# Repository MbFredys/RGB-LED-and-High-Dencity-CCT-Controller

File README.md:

# RGB + CCT LED Controller

Five-channel RGB and tunable-white LED-controller PCB based on the ESP32-C3.

> **Project status:** Design and manufacturing documentation completed. The PCB has not been fabricated, thermally characterized, or electrically validated under load.

## Project objective

The project explores a compact controller capable of driving RGB, warm-white, and cool-white LED channels while integrating wireless control, local power conversion, and USB-C programming.

## Hardware architecture

- **Controller:** ESP32-C3-WROOM-02
- **Outputs:** Five low-side PWM channels: R, G, B, warm white, and cool white
- **Switching devices:** IRLZ44N MOSFETs
- **Power input:** 12 V nominal
- **Conversion:** LM2678T-ADJ buck stage and TPS7A20 3.3 V regulation
- **Programming:** USB-C interface
- **Protection:** Input fuse and transient-protection components
- **Connections:** Dedicated RGB and CCT output connectors

## Engineering work

- Defined the functional and power architecture
- Selected the controller, switching devices, regulators, and protection components
- Developed the schematic and PCB layout in KiCad
- Separated high-current and logic routing
- Prepared the BOM and manufacturing documentation

## Key design considerations

- MOSFET conduction losses and gate drive at 3.3 V
- Copper width, connector rating, and total current distribution
- Regulator thermal performance
- PWM return-current paths
- Bulk capacitance near LED outputs
- ESP32 antenna clearance and noise coupling

## Validation still required

Physical testing is required to establish:

- Safe continuous current per channel
- MOSFET and regulator temperatures
- Voltage-drop and connector performance
- PWM behavior with representative LED strips
- Wireless performance during switching
- Protection response and EMC/EMI behavior

The intended current ratings are design targets and must not be treated as validated operating limits.

## License

Licensed under CERN-OHL-W-2.0.

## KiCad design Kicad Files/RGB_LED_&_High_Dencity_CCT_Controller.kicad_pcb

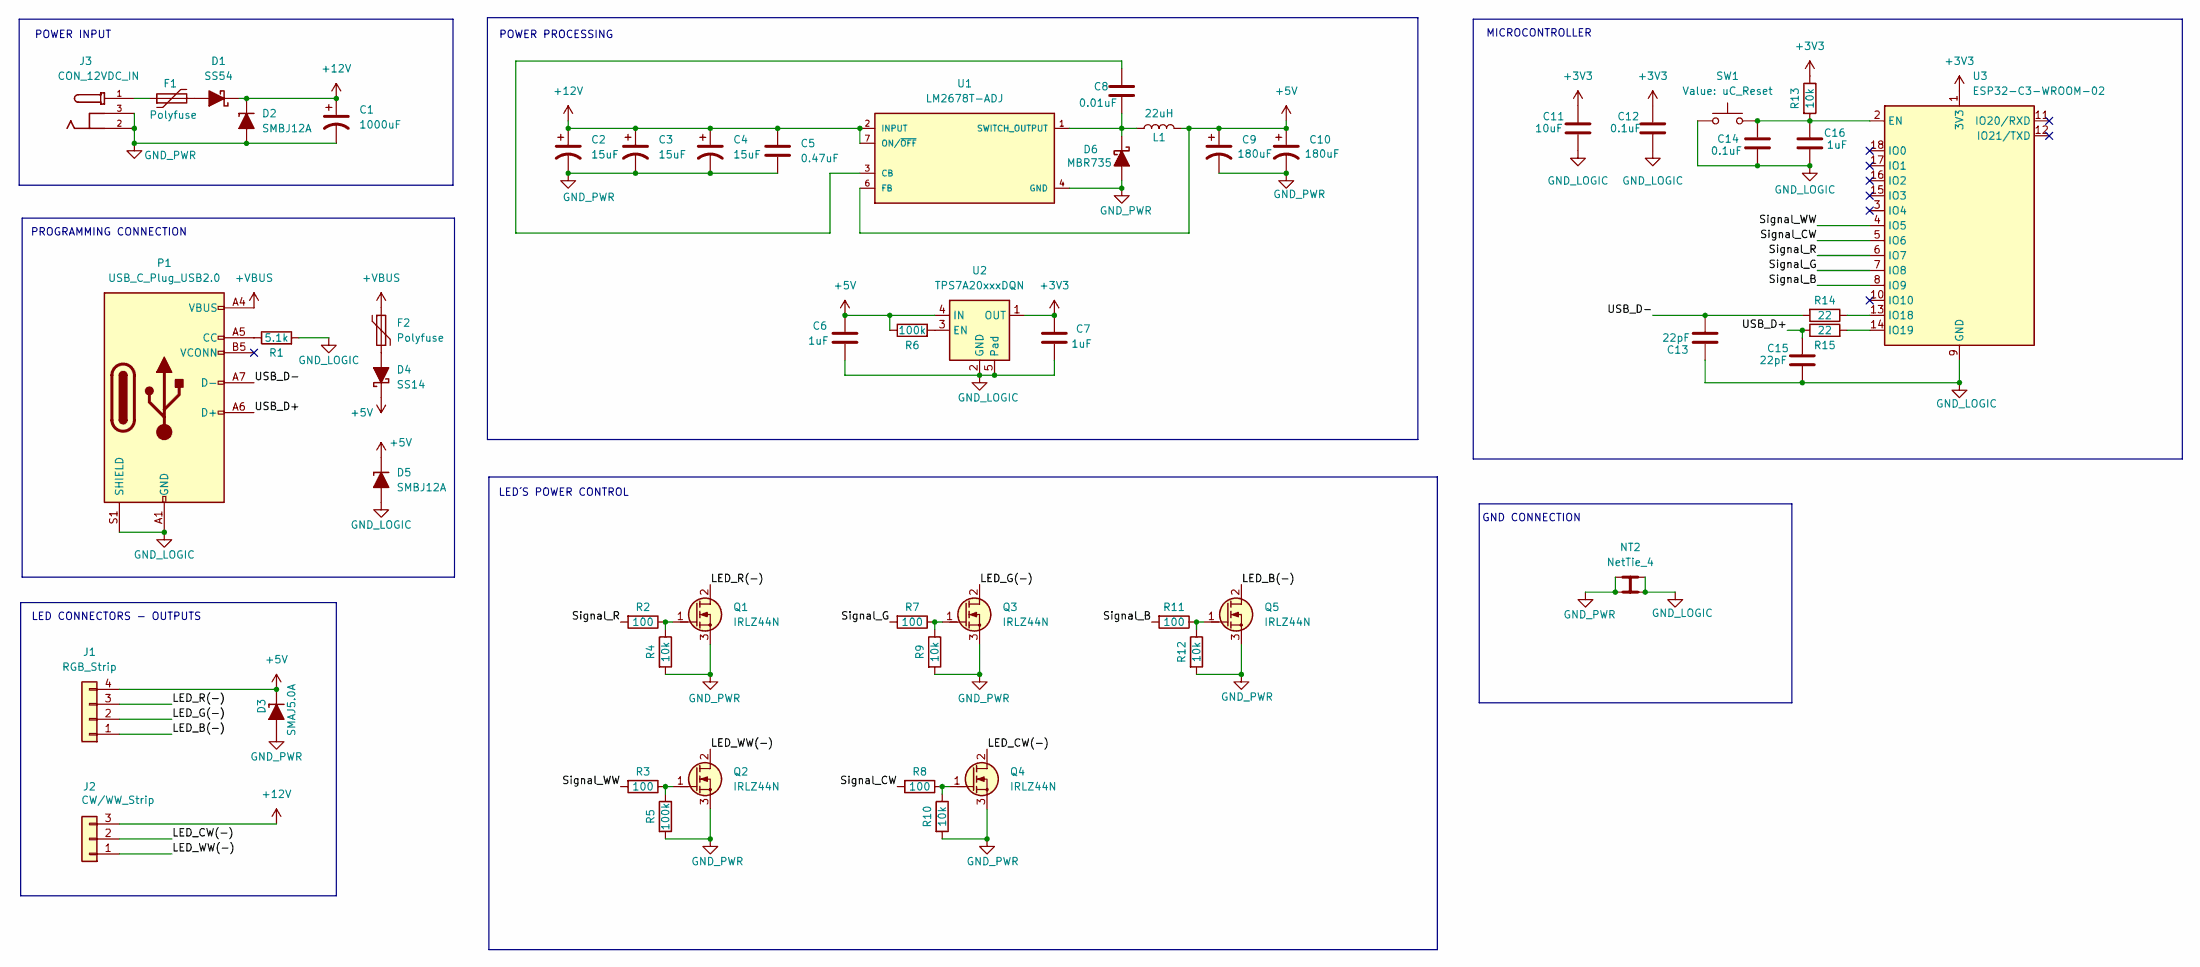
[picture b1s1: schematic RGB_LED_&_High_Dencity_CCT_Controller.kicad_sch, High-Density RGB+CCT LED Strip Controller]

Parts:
C1: 1000uF; CAPPRD500W60D1000H1300; MPN 16SEPF1000M; LCSC PN C128486
C2, C3, C4: 15uF; CAPPRD200W45D500H700; MPN EEA-GA1E150; LCSC PN C1580740
C5: 0.47uF; C_0805_2012Metric; MPN GRM155R71C474KE01D; LCSC PN C471404
C6, C7: 1uF; C_0603_1608Metric; MPN CL10A105KB8NNNC; LCSC PN C15849
C8: 0.01uF; CAPRR750W60L1030T440H750; MPN ECQE4123JF; LCSC PN C48579278
C9, C10: 180uF; CAP_EEEFNE181XUV; MPN EEEFNE181XUV; LCSC PN C540948
C11: 10uF; C_0603_1608Metric; MPN GRM155R71C474KE01D; LCSC PN 0402
C12, C14: 0.1uF; C_0603_1608Metric; MPN GRM155R71C474KE01D; LCSC PN 0402
C13, C15: 22pF; C_0603_1608Metric; MPN GRM155R71C474KE01D; LCSC PN 0402
C16: 1uF; C_0603_1608Metric; MPN GRM155R71C474KE01D; LCSC PN 0402
D1: SS54; D_SMC; MPN SS54; LCSC PN C22452
D2: SMBJ12A; D_SMB; MPN SMBJ12A; LCSC PN C151251
D3: SMAJ5.0A; D_SMA; MPN SMAJ5.0A; LCSC PN C83329
D4: SS14; D_SMA
D5: SMBJ12A; D_SMB
D6: MBR735; TO-220-2_Vertical_KA; MPN MBR735; LCSC PN C3759044
F1: Polyfuse; FUSC7351X170N; MPN 0ZCF0600FF2C; LCSC PN C20040854
F2: Polyfuse; FUSC1608X100N
J1: RGB_Strip; PhoenixContact_MCV_1,5_4-G-5.08_1x04_P5.08mm_Vertical
J2: CW/WW_Strip; PhoenixContact_MCV_1,5_3-G-5.08_1x03_P5.08mm_Vertical
J3: CON_12VDC_IN; MPD_EJ503A; MPN EJ503A; LCSC PN C3095117
L1: 22uH; IND_XAL6060-223MEB; MPN FXL1040-220-M; LCSC PN C475917
NT2: NetTie_4; NetTie-4_THT_Pad1.0mm
P1: USB_C_Plug_USB2.0; USB_C_Receptacle_GCT_USB4105-xx-A_16P_TopMnt_Horizontal
Q1, Q2, Q3, Q4, Q5: IRLZ44N; TO254P1524X483-4N; MPN IRLZ44NSPBF-VB; LCSC PN C19188232
R1: 5.1k; R_0603_1608Metric
R2, R3, R7, R8, R11: 100; R_0402_1005Metric
R4, R9, R10, R12, R13: 10k; R_0603_1608Metric
R5: 100k; R_0603_1608Metric
R6: 100k; R_0805_2012Metric; MPN RC0805FR-07100KL; LCSC PN C96346
R14, R15: 22; R_0402_1005Metric
SW1: uC_Reset; SW_Push_SPST_NO_Alps_SKRK
U1: LM2678T-ADJ; TO127P1041X469X2199-7N
U2: TPS7A20xxxDQN; Texas_X2SON-4_1x1mm_P0.65mm
U3: ESP32-C3-WROOM-02; MPN ESP32-C3-WROOM-02-N4; LCSC PN C2934560

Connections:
+3V3: C7.1, C11.1, C12.1, R13.1, U2.1 (OUT), U3.1 (3V3)
+5V: C6.1, C9.1, C10.1, D3.1 (K), D4.1 (K), D5.1 (K), J1.4, L1.2, R6.1, U1.6 (FB), U2.4 (IN)
+12V: C1.1, C2.1, C3.1, C4.1, C5.1, D1.1 (K), D2.1 (K), J2.3, U1.2 (INPUT), U1.7 (ON/~OFF)
+VBUS: F2.1, P1.A4 (VBUS), P1.A9 (VBUS), P1.B4 (VBUS), P1.B9 (VBUS)
/LED_B(-): J1.1, Q5.2 (D)
/LED_CW(-): J2.2, Q4.2 (D)
/LED_G(-): J1.2, Q3.2 (D)
/LED_R(-): J1.3, Q1.2 (D)
/LED_WW(-): J2.1, Q2.2 (D)
/Signal_B: R11.2, U3.8 (IO9)
/Signal_CW: R8.2, U3.5 (IO6)
/Signal_G: R7.2, U3.7 (IO8)
/Signal_R: R2.2, U3.6 (IO7)
/Signal_WW: R3.2, U3.4 (IO5)
/USB_D+: C15.1, P1.A6 (D+), R15.1
/USB_D-: C13.1, P1.A7 (D-), R14.2
GND_LOGIC: C6.2, C7.2, C11.2, C12.2, C13.2, C14.1, C15.2, C16.2, D5.2 (A), NT2.2, NT2.4, P1.A1 (GND), P1.A12 (GND), P1.B1 (GND), P1.B12 (GND), P1.S1 (SHIELD), R1.2, SW1.1, U2.2 (GND), U2.5 (Pad), U3.9 (GND), U3.19 (GND)
GND_PWR: C1.2, C2.2, C3.2, C4.2, C5.2, C9.2, C10.2, D2.2 (A), D3.2 (A), D6.2 (A), J3.2, J3.3, NT2.1, NT2.3, Q1.3 (S), Q2.3 (S), Q3.3 (S), Q4.3 (S), Q5.3 (S), R4.2, R5.2, R9.2, R10.2, R12.2, U1.4 (GND)
unnamed: D1.2 (A), F1.2
unnamed: D4.2 (A), F2.2
unnamed: C8.2, D6.1 (K), L1.1, U1.1 (SWITCH_OUTPUT)
unnamed: F1.1, J3.1
unnamed: P1.A5 (CC), R1.1
unnamed: Q1.1 (G), R2.1, R4.1
unnamed: Q2.1 (G), R3.1, R5.1
unnamed: Q3.1 (G), R7.1, R9.1
unnamed: Q4.1 (G), R8.1, R10.1
unnamed: Q5.1 (G), R11.1, R12.1
unnamed: C8.1, U1.3 (CB)
unnamed: R6.2, U2.3 (EN)
unnamed: C14.2, C16.1, R13.2, SW1.2, U3.2 (EN)
unnamed: R14.1, U3.13 (IO18)
unnamed: R15.2, U3.14 (IO19)

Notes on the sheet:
POWER PROCESSING
POWER INPUT
GND CONNECTION
LED CONNECTORS - OUTPUTS
LED´S POWER CONTROL
MICROCONTROLLER
PROGRAMMING CONNECTION

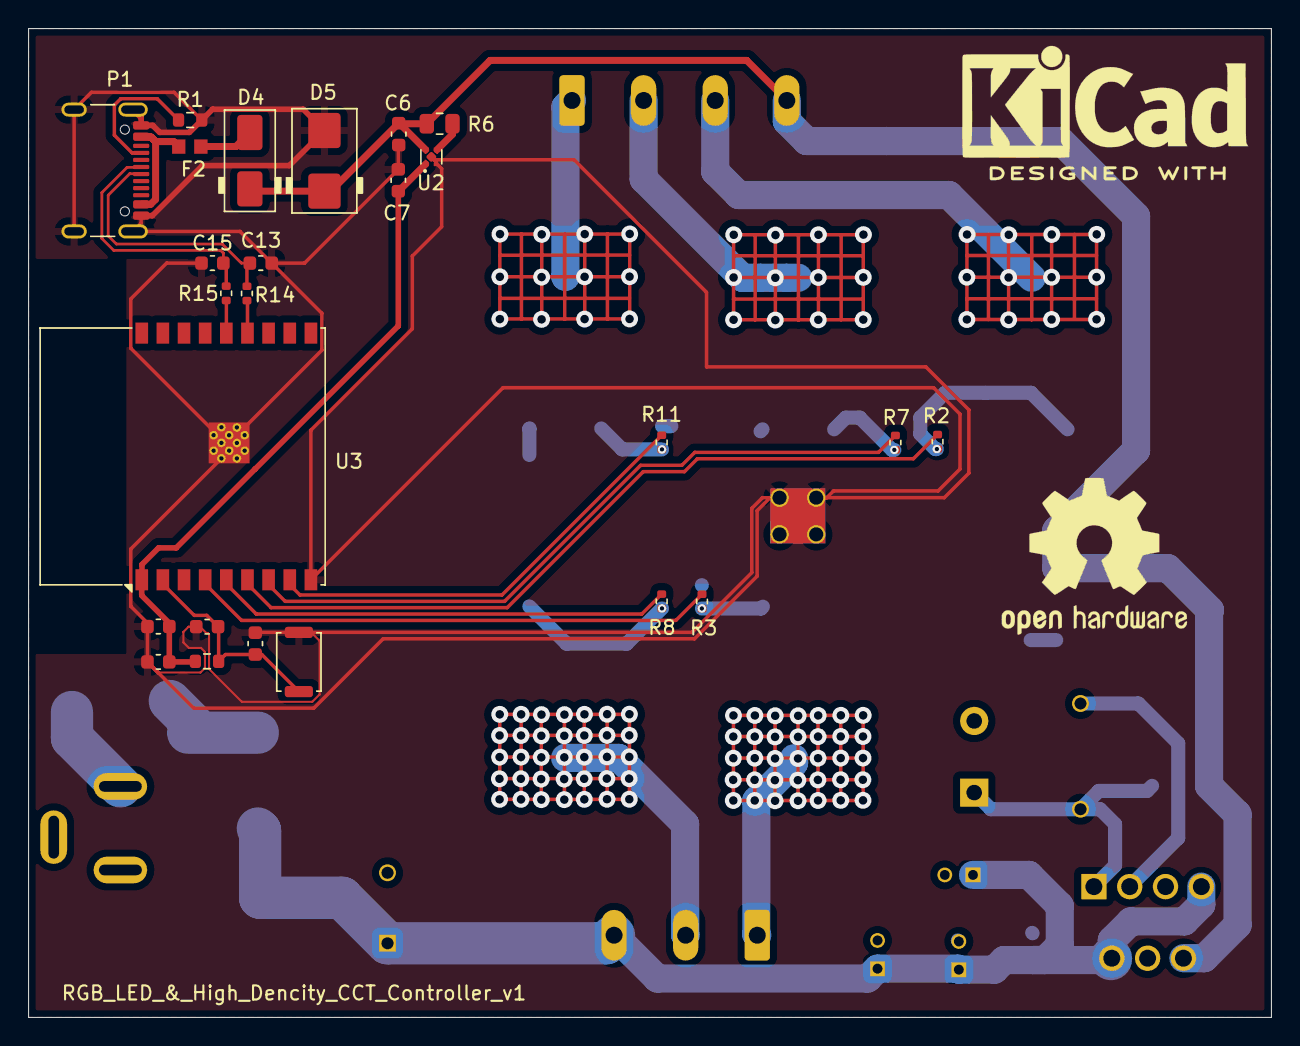
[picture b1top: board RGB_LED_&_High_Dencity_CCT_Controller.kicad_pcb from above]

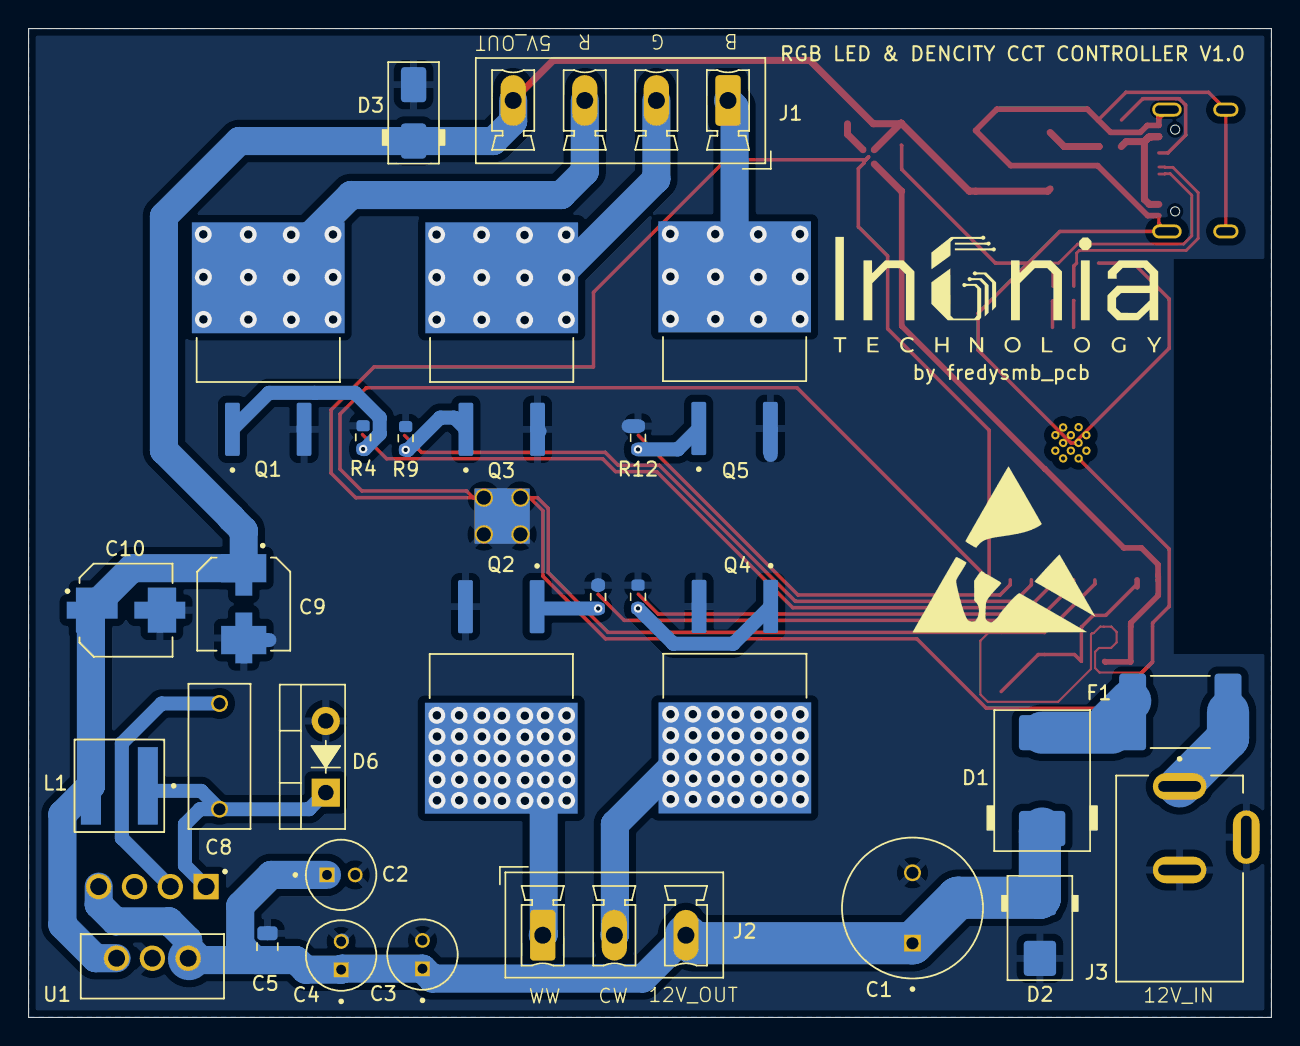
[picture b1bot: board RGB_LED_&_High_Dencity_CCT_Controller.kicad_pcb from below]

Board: 2 copper layers, 88.2 x 70.2 mm, 54 parts (28 on the bottom side), 33 nets.

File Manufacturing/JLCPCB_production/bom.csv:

Designator,Footprint,Quantity,Value,LCSC Part #
C1,CAPPRD500W60D1000H1300,1,1000uF,
"C10, C9",CAP_EEEFNE181XUV,2,180uF,
C11,0603,1,10uF,
"C12, C14",0603,2,0.1uF,
"C13, C15",0603,2,22pF,
"C16, C6, C7",0603,3,1uF,
"C2, C3, C4",CAPPRD200W45D500H700,3,15uF,
C5,0805,1,0.47uF,
C8,CAPRR750W60L1030T440H750,1,0.01uF,
D1,D_SMC,1,SS54,
"D2, D5",D_SMB,2,SMBJ12A,
D3,D_SMA,1,SMAJ5.0A,
D4,D_SMA,1,SS14,
D6,TO-220-2_Vertical_KA,1,MBR735,
F1,FUSC7351X170N,1,Polyfuse,
F2,FUSC1608X100N,1,Polyfuse,
J1,"PhoenixContact_MCV_1,5_4-G-5.08_1x04_P5.08mm_Vertical",1,RGB_Strip,
J2,"PhoenixContact_MCV_1,5_3-G-5.08_1x03_P5.08mm_Vertical",1,CW/WW_Strip,
J3,MPD_EJ503A,1,CON_12VDC_IN,
L1,IND_XAL6060-223MEB,1,22uH,
P1,USB_C_Receptacle_GCT_USB4105-xx-A_16P_TopMnt_Horizontal,1,USB_C_Plug_USB2.0,
"Q1, Q2, Q3, Q4, Q5",TO254P1524X483-4N,5,IRLZ44N,
R1,0603,1,5.1k,
"R10, R12, R13, R4, R9",0603,5,10k,
"R11, R2, R3, R7, R8",0402,5,100,
"R14, R15",0402,2,22,
R5,0603,1,100k,
R6,0805,1,100k,
SW1,SW_Push_SPST_NO_Alps_SKRK,1,uC_Reset,
U1,TO127P1041X469X2199-7N,1,LM2678T-ADJ,
U2,Texas_X2SON-4_1x1mm_P0.65mm,1,TPS7A20xxxDQN,
U3,ESP32-C3-WROOM-02,1,ESP32-C3-WROOM-02,

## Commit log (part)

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2025-10-20 Revise README for PCB-RGB+CCT-LED-Controller
    Updated README to reflect new PCB design and features.
2025-10-20 Add initial firmware documentation
2025-10-21 Add Pictures section to release notes
2025-12-01 Change license from MIT to CERN-OHL-W-2.0
    Updated license information from MIT to CERN Open Hardware Licence Version 2.
2025-12-01 Change license to CERN Open Hardware Licence v2
    Updated license from MIT to CERN Open Hardware Licence Version 2.
2025-12-01 Add CERN Open Hardware Licence Version 2
    Added CERN Open Hardware Licence Version 2 - Weakly Reciprocal to the project.
2025-12-01 Update LICENSE
2025-12-12 Add initial Kicad 9.0 documentation

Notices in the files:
README.md:
License: CERN-OHL-W-2.0
